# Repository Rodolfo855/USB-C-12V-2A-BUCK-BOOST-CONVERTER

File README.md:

USB-C 12V @ 2AM BUCK BOOST CONVERTER

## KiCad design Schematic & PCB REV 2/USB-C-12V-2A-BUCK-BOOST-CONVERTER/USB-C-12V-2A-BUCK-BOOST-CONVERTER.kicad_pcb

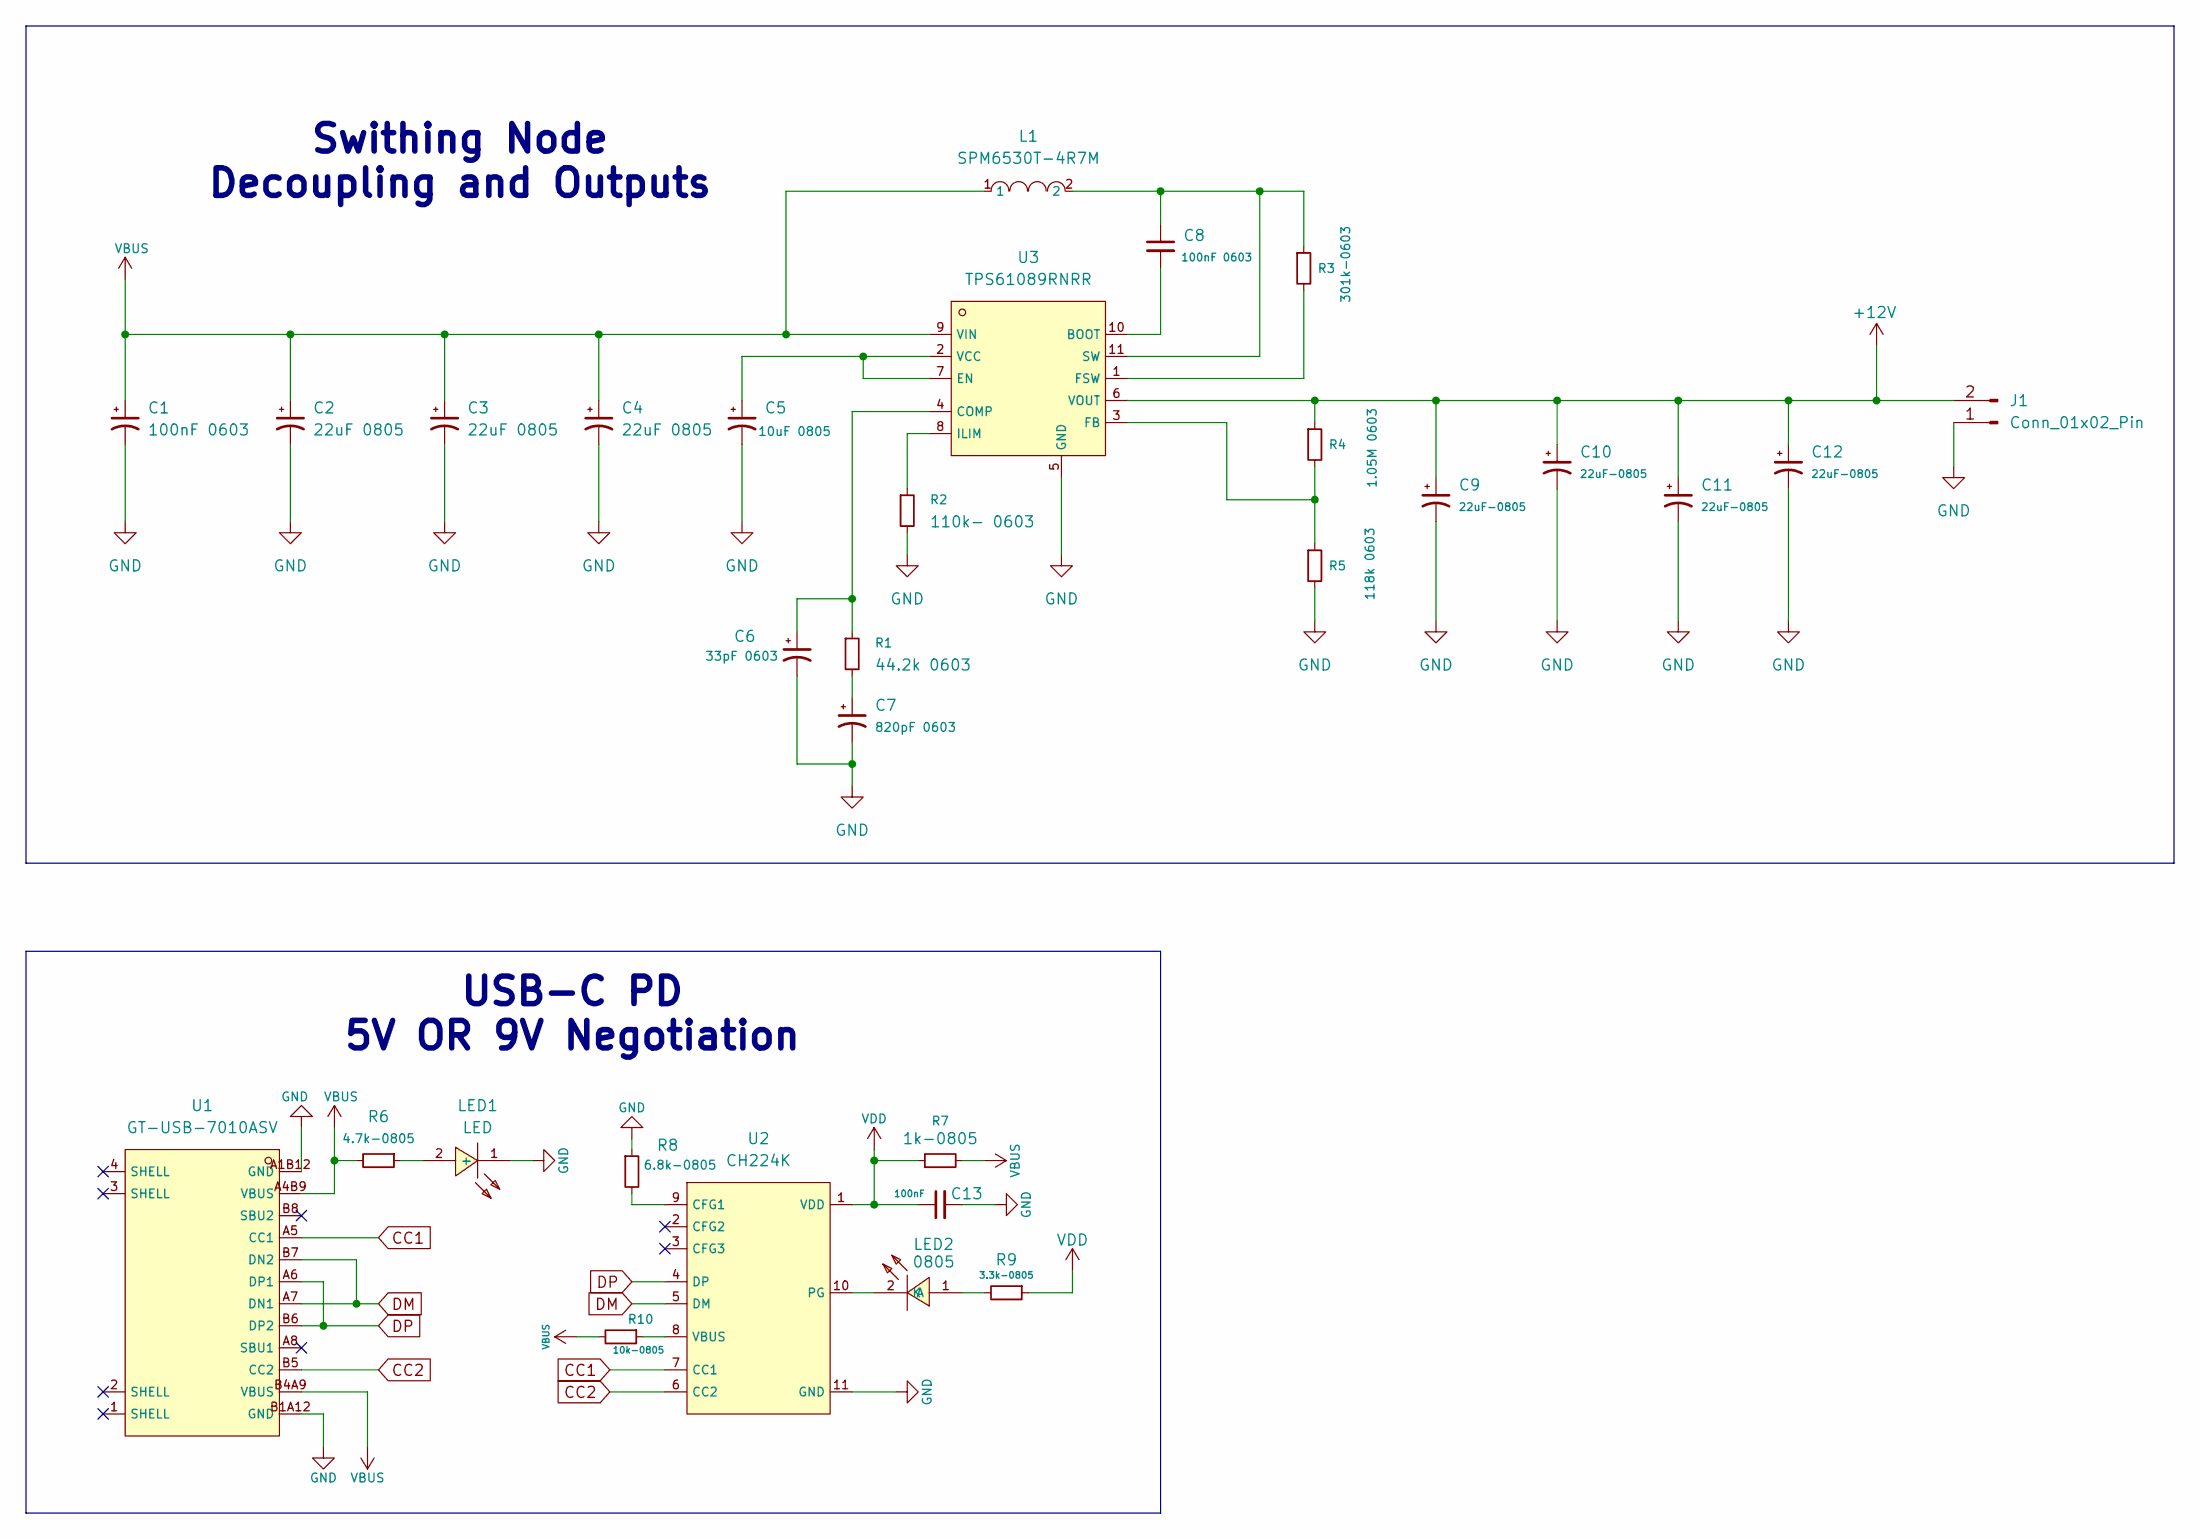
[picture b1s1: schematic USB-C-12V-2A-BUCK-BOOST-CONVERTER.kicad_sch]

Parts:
C1, C8: 100nF 0603; C_0603_1608Metric; LCSC C1591
C2, C3, C4: 22uF 0805; C_0805_2012Metric; LCSC C45783
C5: 10uF 0805; C_0805_2012Metric; LCSC C15850
C6: 33pF 0603; C_0603_1608Metric; LCSC C1663
C7: 820pF 0603; C_0603_1608Metric; LCSC C107057
C9, C10, C11, C12: 22uF-0805; C_0805_2012Metric; LCSC C45783
C13: 100nF; C_0603_1608Metric
J1: Conn_01x02_Pin; JST_XH_B2B-XH-A_1x02_P2.50mm_Vertical
L1: SPM6530T-4R7M; C76857_IND-SMD_L7_1-W6_5; LCSC C76857
LED1: LED; C84256_LED0805-RD; LCSC C84256
LED2: 0805; C2297_LED0805-R-RD; LCSC C2297
R1: 44.2k 0603; R_0603_1608Metric; LCSC C23172
R2: 110k- 0603; R_0603_1608Metric; LCSC C25805
R3: 301k-0603; R_0603_1608Metric; LCSC C23024
R4: 1.05M 0603; R_0603_1608Metric; LCSC C22935
R5: 118k 0603; R_0603_1608Metric; LCSC C25805
R6: 4.7k-0805; R_0805_2012Metric
R7: 1k-0805; R_0805_2012Metric
R8: 6.8k-0805; R_0805_2012Metric
R9: 3.3k-0805; R_0805_2012Metric
R10: 10k-0805; R_0805_2012Metric
U1: GT-USB-7010ASV; C2988369_USB-C-SMD_G-SWITCH_GT-USB-7010ASV; LCSC C2988369
U2: CH224K; C970725_ESSOP-10_L4_9-W3_9-P1_0-LS6_0-TL-EP; LCSC C970725
U3: TPS61089RNRR; C165129_VQFN-HR_L2_5-W2_0-P0_50-TL-EP; LCSC C165129

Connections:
+12V: C9.1, C10.1, C11.1, C12.1, J1.2, R4.1, U3.6 (VOUT)
CC1: U1.A5 (CC1), U2.7 (CC1)
CC2: U1.B5 (CC2), U2.6 (CC2)
DM: U1.A7 (DN1), U1.B7 (DN2), U2.5 (DM)
DP: U1.A6 (DP1), U1.B6 (DP2), U2.4 (DP)
GND: C1.2, C2.2, C3.2, C4.2, C5.2, C6.2, C7.2, C9.2, C10.2, C11.2, C12.2, C13.2, J1.1, LED1.1 (-), R2.2, R5.2, R8.1, U1.A1B12 (GND), U1.B1A12 (GND), U2.11 (GND), U3.5 (GND); also elsewhere on the board
unnamed: C7.1, R1.2
unnamed 7: LED1.2 (+), R6.1; also elsewhere on the board
unnamed 8: LED2.1 (A), R9.2; also elsewhere on the board
unnamed 9: LED2.2 (K), U2.10 (PG); also elsewhere on the board
unnamed: R8.2, U2.9 (CFG1)
unnamed: R10.1, U2.8 (VBUS)
unnamed: C8.2, U3.10 (BOOT)
unnamed: C6.1, R1.1, U3.4 (COMP)
unnamed: C5.1, U3.2 (VCC), U3.7 (EN)
unnamed: R4.2, R5.1, U3.3 (FB)
unnamed: R3.2, U3.1 (FSW)
unnamed: R2.1, U3.8 (ILIM)
unnamed: C8.1, L1.2, R3.1, U3.11 (SW)
VBUS: C1.1, C2.1, C3.1, C4.1, L1.1, R6.2, R7.2, R10.2, U1.A4B9 (VBUS), U1.B4A9 (VBUS), U3.9 (VIN)
VDD: C13.1, R7.1, R9.1, U2.1 (VDD)

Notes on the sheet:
Swithing Node Decoupling and Outputs
USB-C PD 5V OR 9V Negotiation

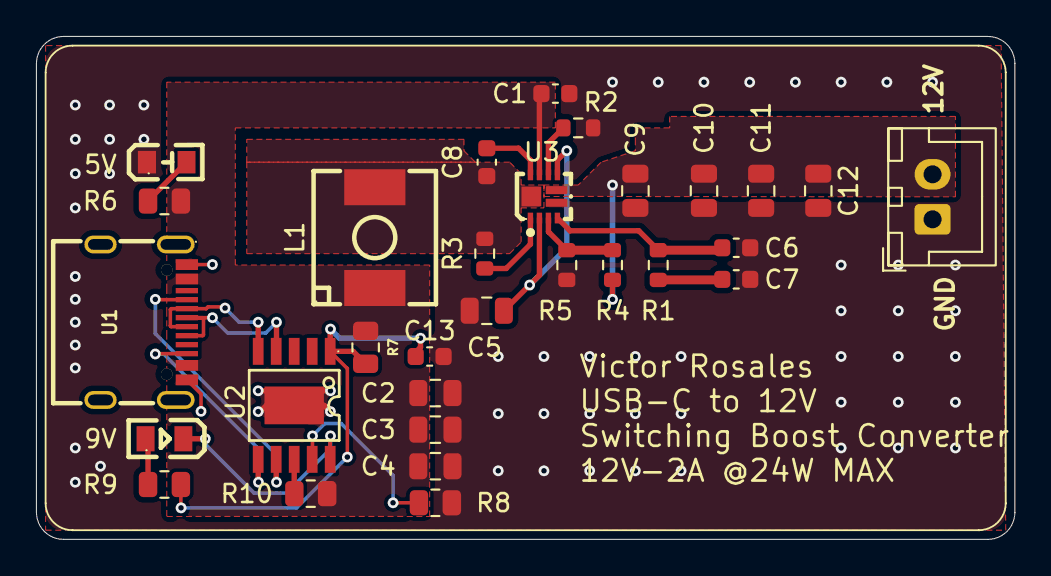
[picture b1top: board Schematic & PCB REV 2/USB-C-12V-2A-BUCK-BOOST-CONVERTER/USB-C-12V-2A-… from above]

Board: 2 copper layers, 54.4 x 27.9 mm, 30 parts (0 on the bottom side), 21 nets.

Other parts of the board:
5V: LED; C84256_LED0805-RD
9V: 0805; C2297_LED0805-R-RD

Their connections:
GND: 5V.1 (-); also elsewhere on the board
unnamed 7: 5V.2 (+); also elsewhere on the board
unnamed 8: 9V.1 (A); also elsewhere on the board
unnamed 9: 9V.2 (K); also elsewhere on the board

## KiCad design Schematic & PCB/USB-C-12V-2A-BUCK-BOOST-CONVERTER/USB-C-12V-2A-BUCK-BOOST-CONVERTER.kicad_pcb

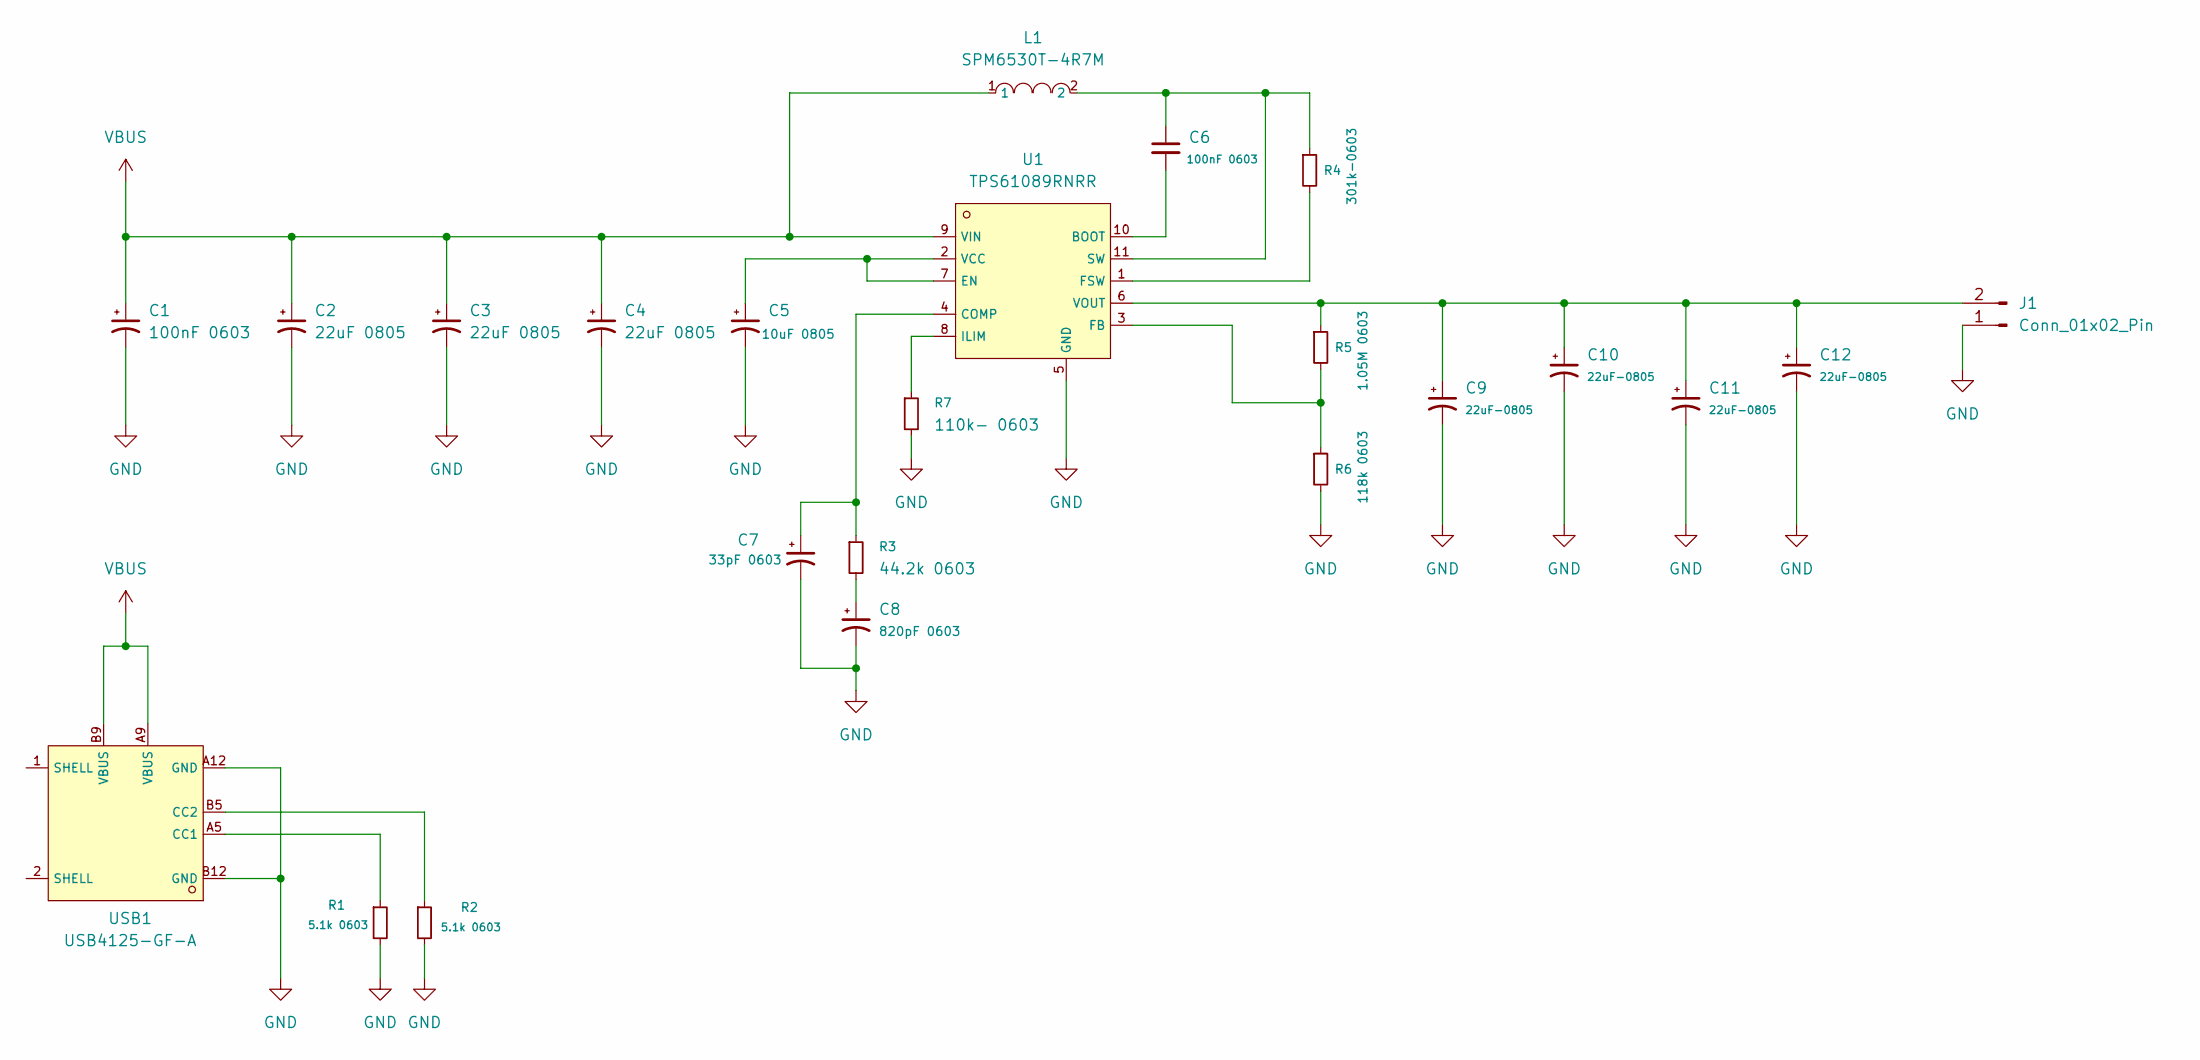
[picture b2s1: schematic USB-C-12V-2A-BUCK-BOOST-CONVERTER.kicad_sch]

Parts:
C1, C6: 100nF 0603; C_0603_1608Metric
C2, C3, C4: 22uF 0805; C_0805_2012Metric
C5: 10uF 0805; C_0805_2012Metric
C7: 33pF 0603; C_0603_1608Metric
C8: 820pF 0603; C_0603_1608Metric
C9: 22uF-0805; C_0603_1608Metric
C10, C11, C12: 22uF-0805; C_0805_2012Metric
J1: Conn_01x02_Pin; JST_XH_B2B-XH-A_1x02_P2.50mm_Vertical
L1: SPM6530T-4R7M; C76857_IND-SMD_L7_1-W6_5; LCSC C76857
R1, R2: 5.1k 0603; R_0603_1608Metric
R3: 44.2k 0603; R_0603_1608Metric
R4: 301k-0603; R_0603_1608Metric
R5: 1.05M 0603; R_0603_1608Metric
R6: 118k 0603; R_0603_1608Metric
R7: 110k- 0603; R_0603_1608Metric
U1: TPS61089RNRR; C165129_VQFN-HR_L2_5-W2_0-P0_50-TL-EP; LCSC C165129
USB1: USB4125-GF-A; C3151650_USB-C-SMD_TYPE-C-6P; LCSC C3151650

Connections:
GND: C1.2, C2.2, C3.2, C4.2, C5.2, C7.2, C8.2, C9.2, C10.2, C11.2, C12.2, J1.1, R1.2, R2.2, R6.2, R7.2, U1.5 (GND), USB1.A12 (GND), USB1.B12 (GND)
unnamed: C8.1, R3.2
unnamed: C9.1, C10.1, C11.1, C12.1, J1.2, R5.1, U1.6 (VOUT)
unnamed: C6.2, U1.10 (BOOT)
unnamed: C7.1, R3.1, U1.4 (COMP)
unnamed: C5.1, U1.2 (VCC), U1.7 (EN)
unnamed: R5.2, R6.1, U1.3 (FB)
unnamed: R4.2, U1.1 (FSW)
unnamed: R7.1, U1.8 (ILIM)
unnamed: C6.1, L1.2, R4.1, U1.11 (SW)
unnamed: R1.1, USB1.A5 (CC1)
unnamed: R2.1, USB1.B5 (CC2)
VBUS: C1.1, C2.1, C3.1, C4.1, L1.1, U1.9 (VIN), USB1.A9 (VBUS), USB1.B9 (VBUS)

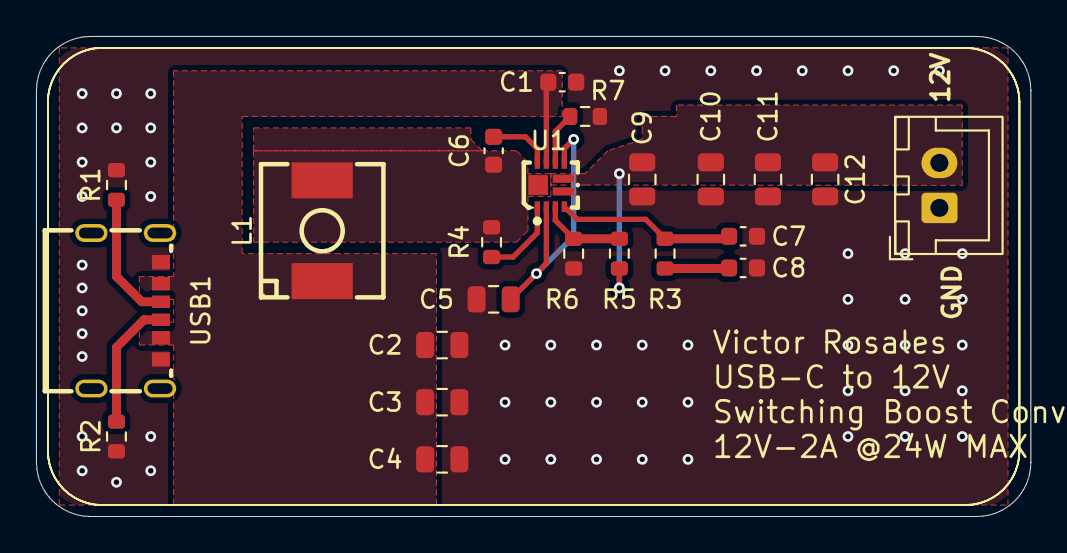
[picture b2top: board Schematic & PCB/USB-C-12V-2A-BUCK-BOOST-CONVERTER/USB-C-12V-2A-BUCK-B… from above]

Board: 2 copper layers, 55.2 x 26.7 mm, 23 parts (0 on the bottom side), 13 nets.
